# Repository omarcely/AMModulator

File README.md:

# AMModulator
Final RF circuits' project of Omar Cely, Diego Figueroa and Felipe González

## Resultados 

A continuación se puede observar el transmisor AM, y observar los resultados del circuito implementado en cada una de las etapas de interés.

## transmisor AM

En el montaje final se observa principalmente la antena, cuyo diametro es de 44 cm y tiene 3 vueltas, además se ve la pequeña placa que implementa el oscilador y el mezclador que mide 5cm x 2.5cm.

### Salida del oscilador

salida del oscilador medida con el analizador de espectros, como se puede ver se tiene una frecuencia de oscilación de 27.6 MHz aproximadamente, sin embargo la frecuencoa es ajustable por medio del inductor variable utilizado.

### Salida del mezclador

salida del mezcaldor medida con un analizador de espectros, y teniendo como mensaje una señal de 15kHz, como resultado se observa la portadora, y varios armónicos del mensaje en las bandas lateralres, podria ser bueno utilizar un filtro pasa bandas para mejorar el desempeño del mezclador

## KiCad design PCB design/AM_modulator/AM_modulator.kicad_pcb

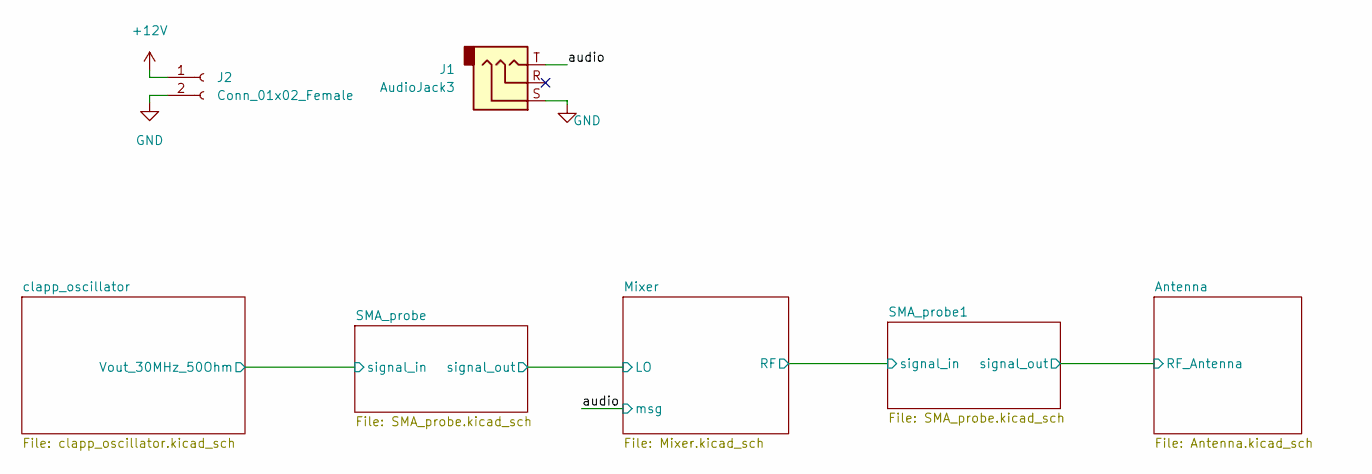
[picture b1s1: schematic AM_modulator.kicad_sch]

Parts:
J1: AudioJack3; Jack_Sigma
J2: Conn_01x02_Female; PinSocket_1x02_P2.54mm_Vertical

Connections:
+12V: J2.1; also elsewhere on the board
/audio: J1.T; also elsewhere on the board
GND: J1.S, J2.2; also elsewhere on the board

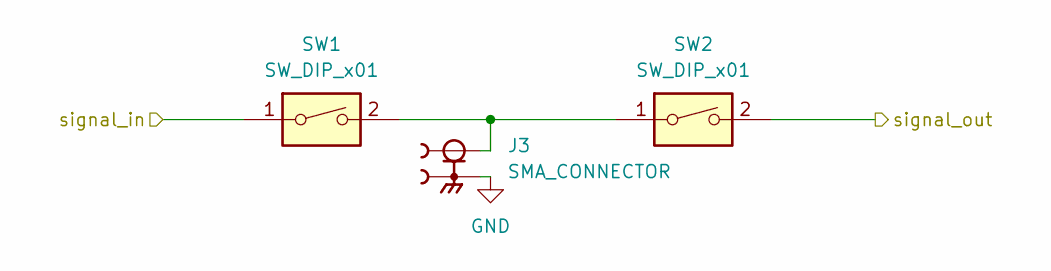
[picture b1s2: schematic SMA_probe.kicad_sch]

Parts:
J3: SMA_CONNECTOR; LPRS_SMA_CONNECTOR; PARTREV 1.3
SW1, SW2: SW_DIP_x01; R_1206_3216Metric

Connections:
/Mixer/LO: SW2.2; also elsewhere on the board
/SMA_probe/signal_in: SW1.1; also elsewhere on the board
GND: J3.G1, J3.G2, J3.G3, J3.G4; also elsewhere on the board
unnamed: J3.1, SW1.2, SW2.1

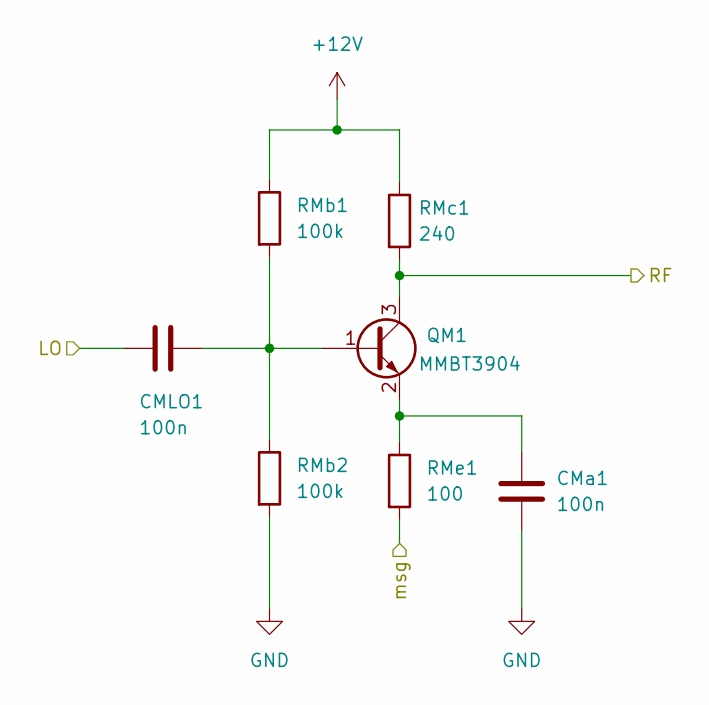
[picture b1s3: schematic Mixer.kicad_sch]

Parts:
CMLO1: 100n; C_0805_2012Metric_Pad1.18x1.45mm_HandSolder
CMa1: 100n; C_0805_2012Metric_Pad1.18x1.45mm_HandSolder
QM1: MMBT3904; SOT-23
RMb1, RMb2: 100k; R_1206_3216Metric_Pad1.30x1.75mm_HandSolder
RMc1: 240; R_1206_3216Metric_Pad1.30x1.75mm_HandSolder
RMe1: 100; R_1206_3216Metric_Pad1.30x1.75mm_HandSolder

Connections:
+12V: RMb1.1, RMc1.1; also elsewhere on the board
/Mixer/LO: CMLO1.2; also elsewhere on the board
/Mixer/RF: QM1.3 (C), RMc1.2; also elsewhere on the board
/audio: RMe1.2; also elsewhere on the board
GND: CMa1.2, RMb2.2; also elsewhere on the board
unnamed: CMLO1.1, QM1.1 (B), RMb1.2, RMb2.1
unnamed: CMa1.1, QM1.2 (E), RMe1.1

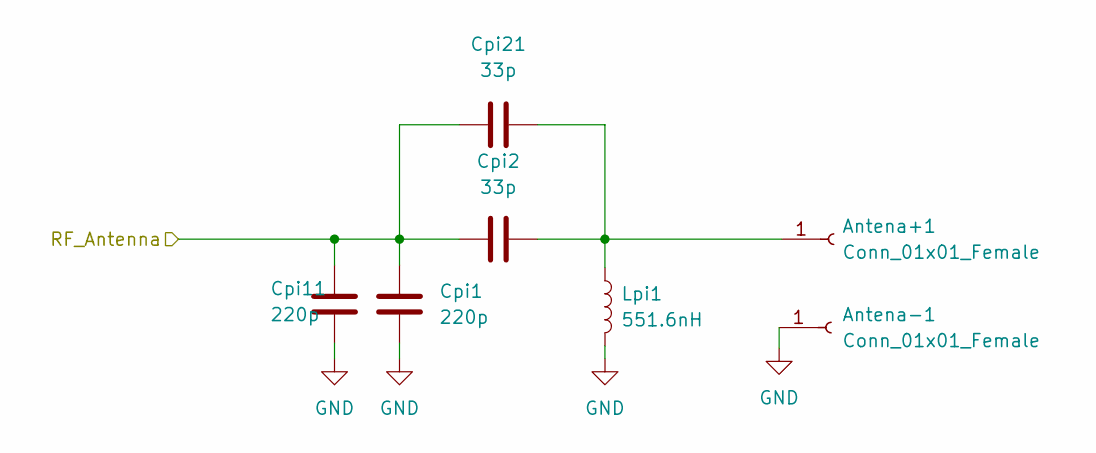
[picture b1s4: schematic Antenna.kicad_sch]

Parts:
Antena+1: Conn_01x01_Female; Pin_D1.4mm_L8.5mm_W2.8mm_FlatFork
Antena-1: Conn_01x01_Female; Pin_D1.4mm_L8.5mm_W2.8mm_FlatFork
Cpi1, Cpi11: 220p; C_0805_2012Metric_Pad1.18x1.45mm_HandSolder
Cpi2, Cpi21: 33p; C_0805_2012Metric_Pad1.18x1.45mm_HandSolder
Lpi1: 551.6nH; L_Toroid_Vertical_L21.6mm_W9.1mm_P8.40mm_Bourns_5700

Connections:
/Antenna/RF_Antenna: Cpi1.1, Cpi2.1, Cpi11.2, Cpi21.1; also elsewhere on the board
GND: Antena-1.1, Cpi1.2, Cpi11.1, Lpi1.2; also elsewhere on the board
unnamed: Antena+1.1, Cpi2.2, Cpi21.2, Lpi1.1

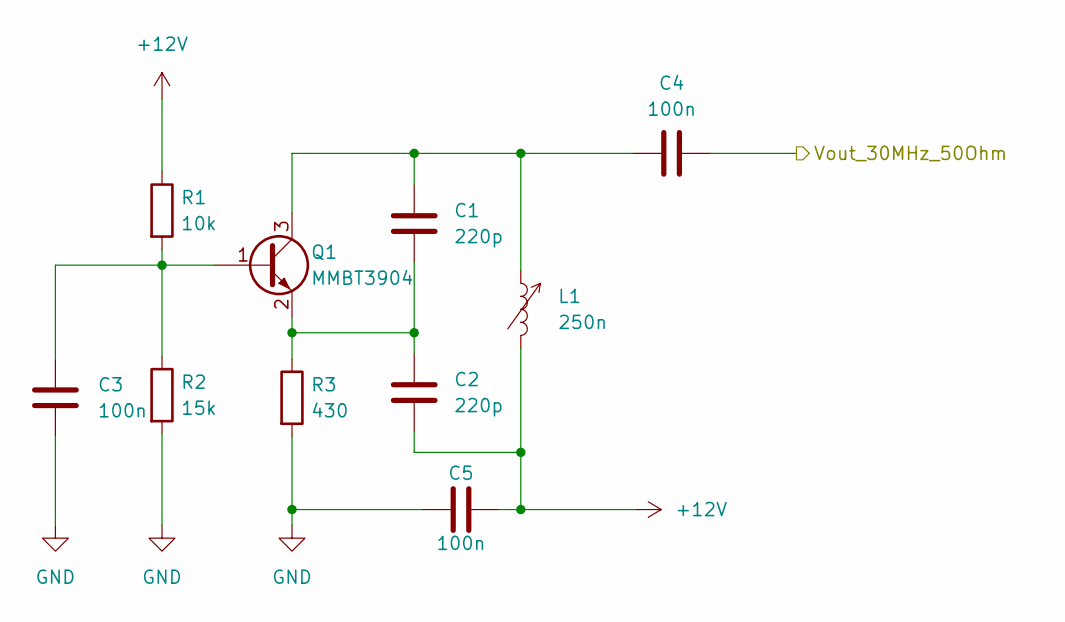
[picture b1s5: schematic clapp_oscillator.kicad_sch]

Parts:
C1, C2: 220p; C_0805_2012Metric_Pad1.18x1.45mm_HandSolder
C3, C4, C5: 100n; C_0805_2012Metric_Pad1.18x1.45mm_HandSolder
L1: 250n; variable_inductor
Q1: MMBT3904; SOT-23
R1: 10k; R_1206_3216Metric_Pad1.30x1.75mm_HandSolder
R2: 15k; R_1206_3216Metric_Pad1.30x1.75mm_HandSolder
R3: 430; R_1206_3216Metric_Pad1.30x1.75mm_HandSolder

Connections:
+12V: C2.2, C5.2, L1.2, R1.1; also elsewhere on the board
/SMA_probe/signal_in: C4.2; also elsewhere on the board
GND: C3.2, C5.1, R2.2, R3.2; also elsewhere on the board
unnamed: C1.1, C4.1, L1.1, Q1.3 (C)
unnamed: C1.2, C2.1, Q1.2 (E), R3.1
unnamed: C3.1, Q1.1 (B), R1.2, R2.1

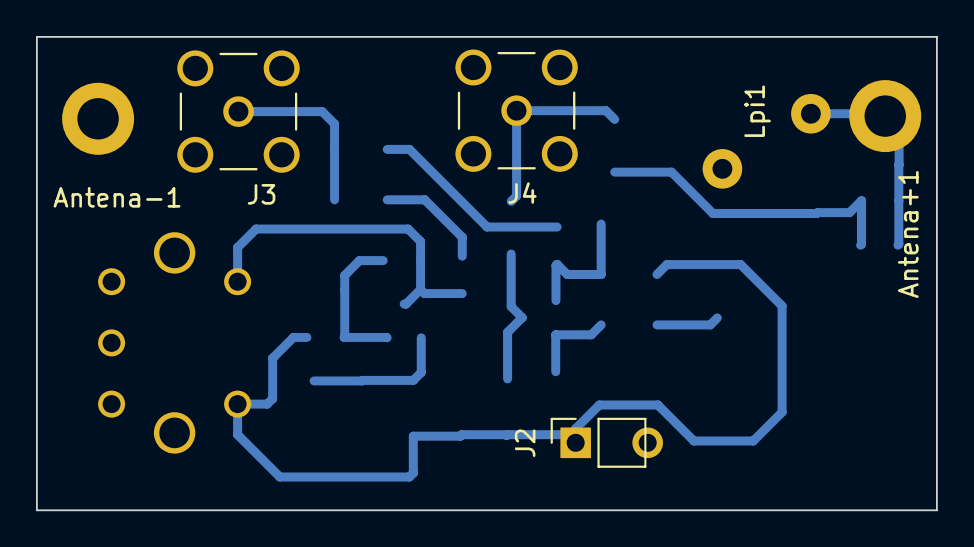
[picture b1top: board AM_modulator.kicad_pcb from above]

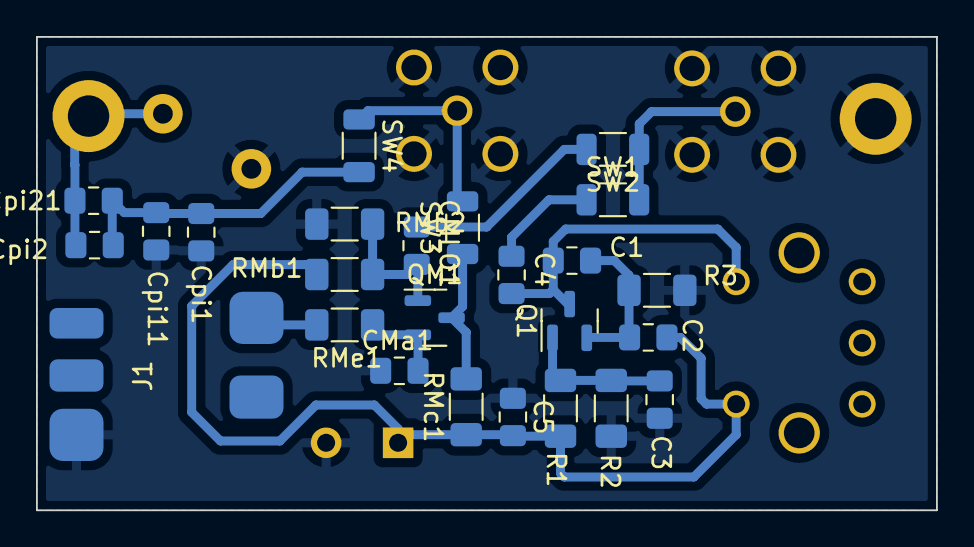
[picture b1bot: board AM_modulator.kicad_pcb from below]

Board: 2 copper layers, 50.0 x 26.3 mm, 32 parts (25 on the bottom side), 15 nets.

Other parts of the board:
J4: SMA_CONNECTOR; LPRS_SMA_CONNECTOR
SW3, SW4: SW_DIP_x01; R_1206_3216Metric

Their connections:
/Antenna/RF_Antenna: SW4.2; also elsewhere on the board
/Mixer/RF: SW3.1; also elsewhere on the board
GND: J4.G1, J4.G2, J4.G3, J4.G4; also elsewhere on the board
unnamed: J4.1, SW3.2, SW4.1

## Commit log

2022-06-16 Just the basic folders
2022-06-19 BJT model, BJT datasheet and BJT characterization
2022-06-19 oscillator designed
2022-06-20 begin of PCB design -- oscillator
2022-06-20 oscillator PCB design done
2022-06-20 simulation fix
2022-06-22 change in f0
2022-06-22 Mixer
    Con BJT y entrada por la base
2022-06-22 matlab scripts for oscillator design
2022-06-24 Created oscilator file
2022-06-25 New mixer topology. Seems more stable
2022-06-28 Mixer en la placa
    Integración del mezclador en la placa
2022-06-28 oscillator design impruvment
2022-06-28 mixer
2022-06-28 Nothing useful
2022-06-28 Avances placa
2022-06-28 Antenna march sim
2022-06-28 Antenna Match with practical values
2022-06-28 Nothing
2022-06-28 Antenna matching script uploaded
2022-06-28 Placa terminada
2022-06-29 PCB 2.0
2022-06-30 "Reduced design Q to approx10.5"
2022-06-30 "Just updated the Antenna sim"
2022-07-01 PCB design done
2022-07-05 PCB corregida
